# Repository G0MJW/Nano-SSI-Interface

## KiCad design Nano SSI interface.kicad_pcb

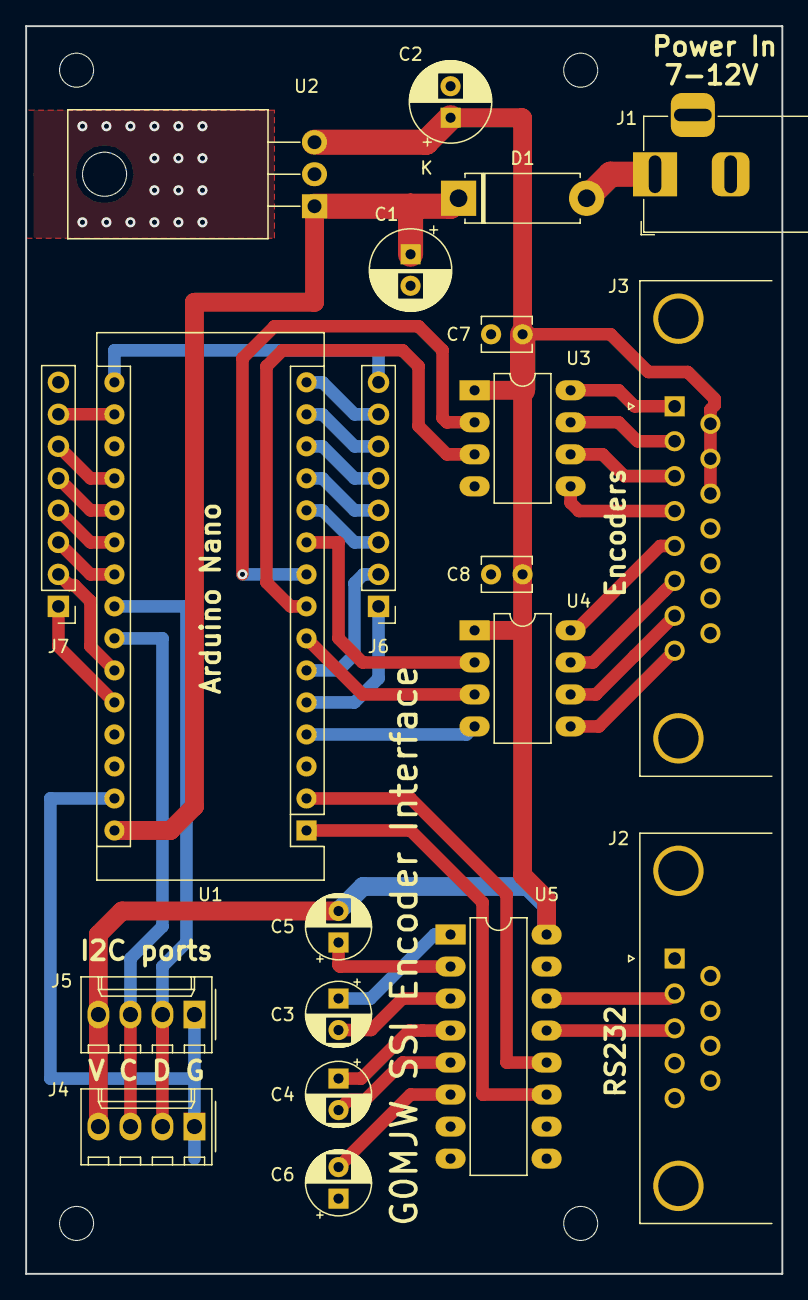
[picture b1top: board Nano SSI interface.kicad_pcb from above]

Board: 2 copper layers, 60.0 x 99.0 mm, 21 parts (0 on the bottom side), 43 nets.

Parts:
C1, C2: 10uF; CP_Radial_D6.3mm_P2.50mm
C3, C4, C5, C6: 10uF; CP_Radial_D5.0mm_P2.50mm
C7: 100n; C_Disc_D3.8mm_W2.6mm_P2.50mm
C8: 100nF; C_Disc_D3.8mm_W2.6mm_P2.50mm
D1: 1N4001; D_5W_P10.16mm_Horizontal
J1: Conn_Coaxial_Power; BarrelJack_Horizontal
J2: DB9_Female_MountingHoles; DSUB-9_Female_Horizontal_P2.77x2.84mm_EdgePinOffset4.94mm_H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
J3: DB15_Female_MountingHoles; DSUB-15_Female_Horizontal_P2.77x2.84mm_EdgePinOffset4.94mm_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
J4, J5: Conn_01x04_Male; Molex_KK-254_AE-6410-04A_1x04_P2.54mm_Vertical
J6, J7: Conn_01x08_Male; PinHeader_1x08_P2.54mm_Vertical
U1: Arduino_Nano_v3.x; Arduino_Nano
U2: LM7805_TO220; TO-220-3_Horizontal_TabDown
U3, U4: SN75179B; DIP-8_W7.62mm_LongPads
U5: MAX232; DIP-16_W7.62mm_LongPads

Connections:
+5V: C2.1, C5.2, C7.1, C8.1, J3.9, J3.10, J3.11, J4.4, J5.4, U2.3, U3.1, U4.1, U5.16
GND: C1.2, C2.2, C6.1, C7.2, C8.2, J1.2, J2.0, J2.5, J3.0, J3.12, J3.13, J3.14, J3.15, J4.1, J5.1, J7.8, U1.4, U1.29, U2.2, U3.4, U4.4, U5.15
unnamed: C1.1, D1.1, U1.30, U2.1
unnamed: C3.1, U5.1
unnamed: C3.2, U5.3
unnamed: C4.1, U5.4
unnamed: C4.2, U5.5
unnamed: C5.1, U5.2
unnamed: C6.2, U5.6
unnamed: D1.2, J1.1
unnamed: J2.2, U5.14
unnamed: J2.3, U5.13
unnamed: J3.1, U3.8
unnamed: J3.2, U3.7
unnamed: J3.3, U3.6
unnamed: J3.4, U3.5
unnamed: J3.5, U4.8
unnamed: J3.6, U4.7
unnamed: J3.7, U4.6
unnamed: J3.8, U4.5
unnamed: J4.2, J5.2, U1.23
unnamed: J4.3, J5.3, U1.24
unnamed: J6.1, U1.5
unnamed: J6.2, U1.6
unnamed: J6.3, U1.11
unnamed: J6.4, U1.12
unnamed: J6.5, U1.13
unnamed: J6.6, U1.14
unnamed: J6.7, U1.15
unnamed: J6.8, U1.16
unnamed: J7.1, U1.26
unnamed: J7.2, U1.25
unnamed: J7.3, U1.22
unnamed: J7.4, U1.21
unnamed: J7.5, U1.20
unnamed: J7.6, U1.19
unnamed: J7.7, U1.17
unnamed: U1.1, U5.11
unnamed: U1.2, U5.12
unnamed: U1.7, U4.3
unnamed: U1.8, U3.3
unnamed: U1.9, U3.2
unnamed: U1.10, U4.2

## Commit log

2019-08-20 3D Fixes
2020-01-05 Update fp-info-cache
